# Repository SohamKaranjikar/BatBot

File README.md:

# BatBot
Hardware and Firmware for research regarding B2 (BatBot) under Post Doc. Jonathan Hoff and Prof.Joohyung Kim

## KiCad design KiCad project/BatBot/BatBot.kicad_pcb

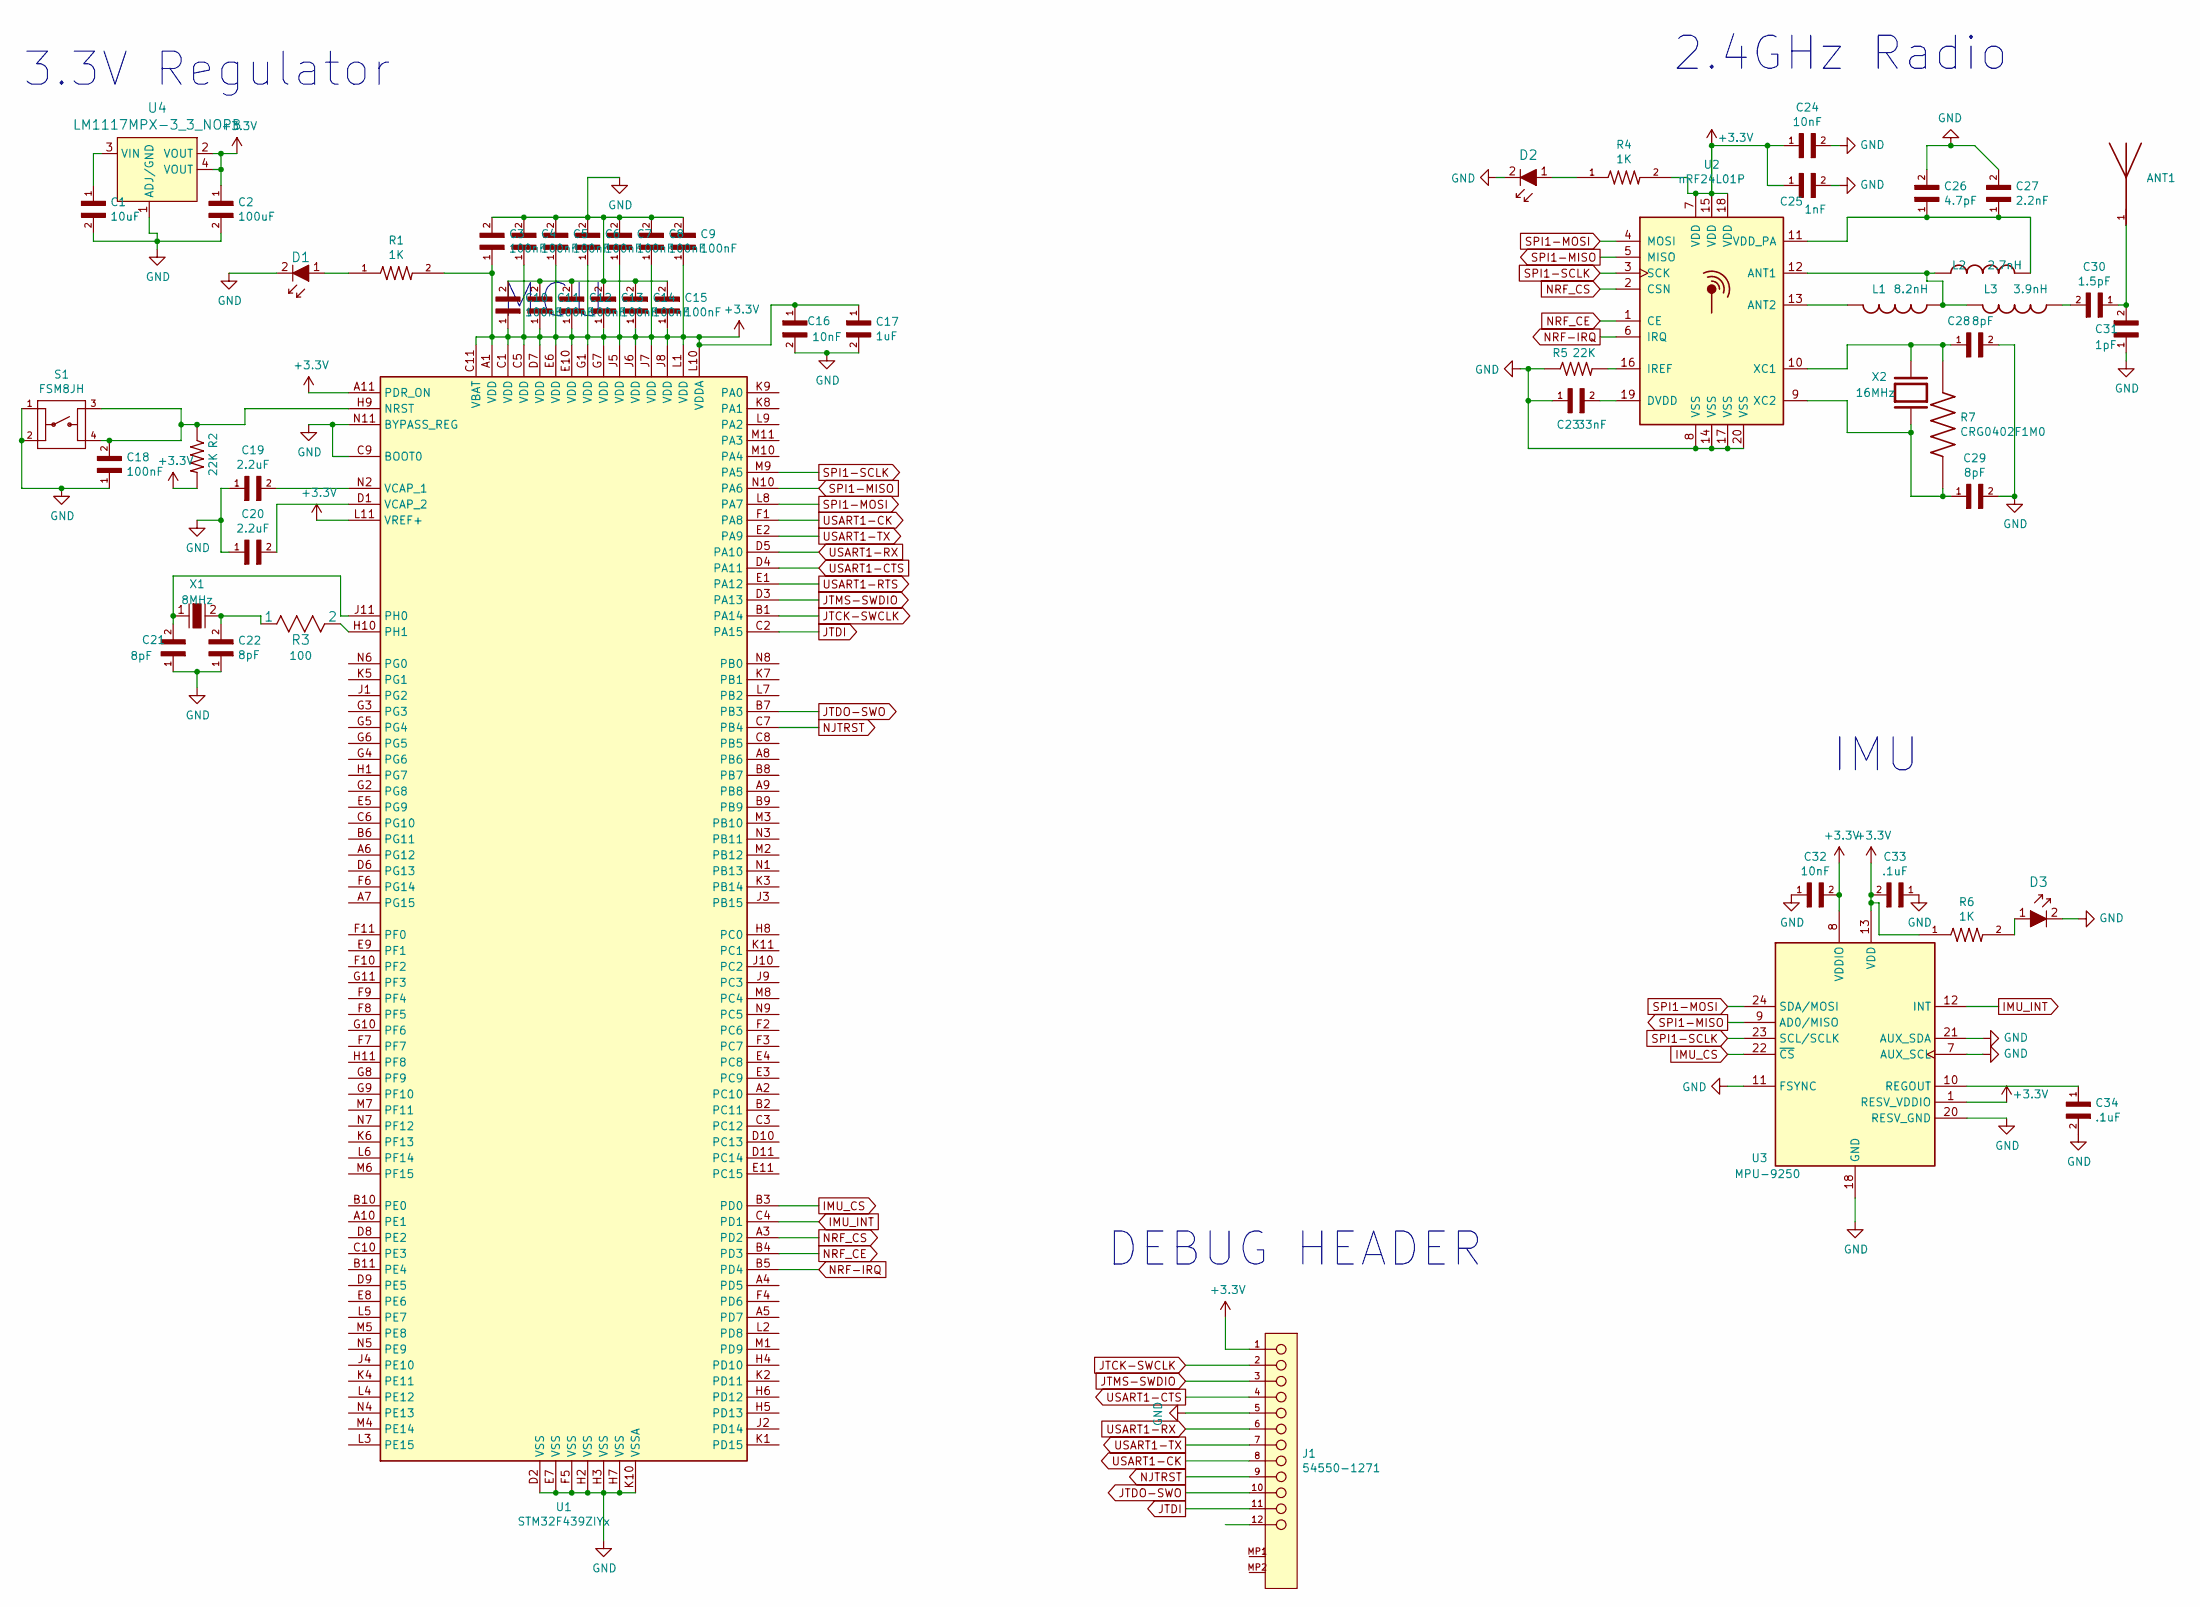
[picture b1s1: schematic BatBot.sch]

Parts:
ANT1: AMCA31-2R450G-S1F-T3; ANT_AMCA31-2R450G-S1F-T3
C1: GCJ21BR71A106KE01L; CAPC2012X145N
C2: CL31A107MQHNNNE; CAPC3216X180N
C3, C4, C5, C6, C7, C8, C9, C10, C11, C12, C13, C14, C15, C18: GCE21BR71H104KA01L; CAPC2012X145N
C16, C24, C32: 06035C103MAT2A; CAPC1608X90N
C17: GCM21BR11E105KA42L; CAPC2012X140N
C19, C20: GRM188C71E225KE11J; CAPC1608X100N
C21, C22, C28, C29: GRM0335C1H8R0DA01D; CAPC0603X33N
C23: 06035C333KAT2A; CAPC1608X90N
C25: 0402ZC102KAT2A; CAPC1005X56N
C26: CC0603BRNPO0BN4R7; CAPC1608X90
C27: EMK212B7225MG-T; CAPC2012X135N
C30: AC0402BRNPO9BN1R5; CAPC1005X55N
C31: CC0603CRNPO8BN1R0; CAPC1608X90
C33, C34: 0805YC104K4Z4A; CAPC2012X140N
D1, D2, D3: LTST-C190KRKT; 0603; MPN LTST-C190KRKT; Digi-Key_PN 160-1436-1-ND
J1: 54550-1271; Molex-54550-1271-Manufacturer_Recommended; Voltage Max 50V
L1: CE201210-8N2J; INDC2012X103N
L2: AQ1052N7S-T; INDC1006X55N
L3: AIMC-0805-3N9S-T; INDC2012X115N
R1, R4, R6: 1-1622826-8; RESC1005X35N
R2, R5: 8-1676481-3; RESC1608X50N
R3: RC0201FR-07100RL
R7: CRG0402F1M0; RESC1005X40N
S1: FSM8JH; SW_FSM8JH
U1: STM32F439ZIYx; ST_WLCSP-143_Die419
U2: nRF24L01P; QFN-20-1EP_4x4mm_P0.5mm_EP2.5x2.5mm
U3: MPU-9250; InvenSense_QFN-24_3x3mm_P0.4mm
U4: LM1117MPX-3_3_NOPB; SOT-223; MPN LM1117MPX-3.3/NOPB; Digi-Key_PN LM1117MPX-3.3/NOPBCT-ND
X1: NX3225GD-8MHZ-STD-CRA-3; SMD-2_3.2x2.5mm; MPN NX3225GD-8MHZ-STD-CRA-3; Digi-Key_PN 644-1178-1-ND
X2: XRCHA16M000F0A01R0; OSC_XRCHA16M000F0A01R0

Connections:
+3V3: C2.1, C3.1, C4.1, C5.1, C6.1, C7.1, C8.1, C9.1, C10.1, C11.1, C12.1, C13.1, C14.1, C15.1, C16.1, C17.1, C24.1, C25.1, C32.2, C33.2, J1.1, R1.2, R2.2, R4.2, R6.1, U1.A1 (VDD), U1.A11 (PDR_ON), U1.C1 (VDD), U1.C5 (VDD), U1.C11 (VBAT), U1.D7 (VDD), U1.E6 (VDD), U1.E10 (VDD), U1.G1 (VDD), U1.G7 (VDD), U1.J5 (VDD), U1.J6 (VDD), U1.J7 (VDD), U1.J8 (VDD), U1.L1 (VDD), U1.L10 (VDDA), U1.L11 (VREF+), U2.7 (VDD), U2.15 (VDD), U2.18 (VDD), U3.1 (RESV_VDDIO), U3.8 (VDDIO), U3.13 (VDD), U4.2 (VOUT), U4.4 (VOUT)
GND: C1.2, C2.2, C3.2, C4.2, C5.2, C6.2, C7.2, C8.2, C9.2, C10.2, C11.2, C12.2, C13.2, C14.2, C15.2, C16.2, C17.2, C18.1, C19.1, C20.1, C21.1, C22.1, C23.1, C24.2, C25.2, C26.2, C27.2, C28.2, C29.2, C31.1, C32.1, C33.1, C34.2, D1.2, D2.2, D3.2, J1.5, R5.1, S1.1, S1.2, U1.C9 (BOOT0), U1.D2 (VSS), U1.E7 (VSS), U1.F5 (VSS), U1.H2 (VSS), U1.H3 (VSS), U1.H7 (VSS), U1.K10 (VSSA), U1.N11 (BYPASS_REG), U2.8 (VSS), U2.14 (VSS), U2.17 (VSS), U2.20 (VSS), U3.7 (AUX_SCL), U3.11 (FSYNC), U3.18 (GND), U3.20 (RESV_GND), U3.21 (AUX_SDA), U4.1 (ADJ/GND)
IMU_CS: U1.B3 (PD0), U3.22 (~CS)
IMU_INT: U1.C4 (PD1), U3.12 (INT)
JTDO-SWO: J1.10, U1.B7 (PB3)
JTMS-SWDIO: J1.3, U1.D3 (PA13)
NJTRST: J1.9, U1.C7 (PB4)
NRF-IRQ: U1.B5 (PD4), U2.6 (IRQ)
NRF_CE: U1.B4 (PD3), U2.1 (CE)
NRF_CS: U1.A3 (PD2), U2.2 (CSN)
unnamed: ANT1.1, C30.1, C31.2
unnamed: C1.1, U4.3 (VIN)
unnamed: C18.2, R2.1, S1.3, S1.4, U1.H9 (NRST)
unnamed: C19.2, U1.N2 (VCAP_1)
unnamed: C20.2, U1.D1 (VCAP_2)
unnamed: C21.2, U1.J11 (PH0), X1.1
unnamed: C22.2, R3.1, X1.2
unnamed: C23.2, U2.19 (DVDD)
unnamed: C26.1, C27.1, L2.1, U2.11 (VDD_PA)
unnamed: C28.1, R7.1, U2.10 (XC1), X2.1
unnamed: C29.1, R7.2, U2.9 (XC2), X2.2
unnamed: C30.2, L3.2
unnamed: C34.1, U3.10 (REGOUT)
unnamed: D1.1, R1.1
unnamed: D2.1, R4.1
unnamed: D3.1, R6.2
unnamed: L1.1, U2.13 (ANT2)
unnamed: L1.2, L2.2, L3.1, U2.12 (ANT1)
unnamed: R3.2, U1.H10 (PH1)
unnamed: R5.2, U2.16 (IREF)
SPI1-MISO: U1.N10 (PA6), U2.5 (MISO), U3.9 (AD0/MISO)
SPI1-MOSI: U1.L8 (PA7), U2.4 (MOSI), U3.24 (SDA/MOSI)
SPI1-SCLK: U1.M9 (PA5), U2.3 (SCK), U3.23 (SCL/SCLK)
USART1-CK: J1.8, U1.F1 (PA8)
USART1-CTS: J1.4, U1.D4 (PA11)
USART1-RTS: U1.E1 (PA12)
USART1-RX: J1.6, U1.D5 (PA10)
USART1-TX: J1.7, U1.E2 (PA9)

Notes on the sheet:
2.4GHz Radio
IMU
3.3V Regulator
MCU
DEBUG HEADER

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
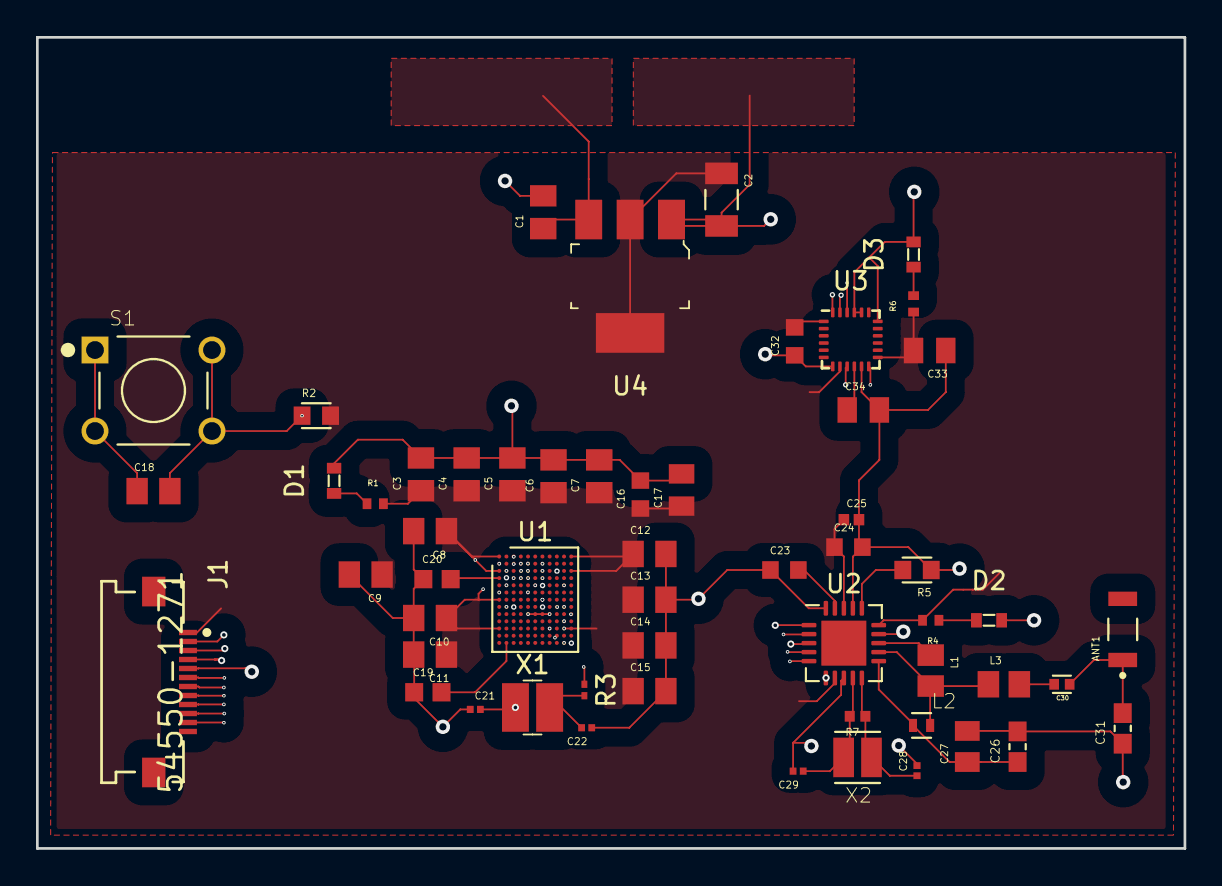
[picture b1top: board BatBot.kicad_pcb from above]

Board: 4 copper layers, 63.8 x 45.1 mm, 56 parts (0 on the bottom side), 38 nets.

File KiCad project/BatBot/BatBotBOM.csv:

"Source:","/Users/Soham/Desktop/School/ECE 397 B2/KiCad project/BatBot/BatBot.sch"
"Date:","Wednesday, September 30, 2020 at 10:15:36 PM"
"Tool:","Eeschema (5.1.6-0)"
"Component Count:","55"
"Ref","Value","Footprint","Datasheet","Manufacturer","Vendor"
"ANT1","AMCA31-2R450G-S1F-T3","ANT_AMCA31-2R450G-S1F-T3","1.4mm","",""
"C1","GCJ21BR71A106KE01L","CAPC2012X145N","","",""
"C2","CL31A107MQHNNNE","CAPC3216X180N","","",""
"C3","GCE21BR71H104KA01L","CAPC2012X145N","","",""
"C4","GCE21BR71H104KA01L","CAPC2012X145N","","",""
"C5","GCE21BR71H104KA01L","CAPC2012X145N","","",""
"C6","GCE21BR71H104KA01L","CAPC2012X145N","","",""
"C7","GCE21BR71H104KA01L","CAPC2012X145N","","",""
"C8","GCE21BR71H104KA01L","CAPC2012X145N","","",""
"C9","GCE21BR71H104KA01L","CAPC2012X145N","","",""
"C10","GCE21BR71H104KA01L","CAPC2012X145N","","",""
"C11","GCE21BR71H104KA01L","CAPC2012X145N","","",""
"C12","GCE21BR71H104KA01L","CAPC2012X145N","","",""
"C13","GCE21BR71H104KA01L","CAPC2012X145N","","",""
"C14","GCE21BR71H104KA01L","CAPC2012X145N","","",""
"C15","GCE21BR71H104KA01L","CAPC2012X145N","","",""
"C16","06035C103MAT2A","CAPC1608X90N","","",""
"C17","GCM21BR11E105KA42L","CAPC2012X140N","","",""
"C18","GCE21BR71H104KA01L","CAPC2012X145N","","",""
"C19","GRM188C71E225KE11J","CAPC1608X100N","","",""
"C20","GRM188C71E225KE11J","CAPC1608X100N","","",""
"C21","GRM0335C1H8R0DA01D","CAPC0603X33N","","",""
"C22","GRM0335C1H8R0DA01D","CAPC0603X33N","","",""
"C23","06035C333KAT2A","CAPC1608X90N","","",""
"C24","06035C103MAT2A","CAPC1608X90N","","",""
"C25","0402ZC102KAT2A","CAPC1005X56N","","",""
"C26","CC0603BRNPO0BN4R7","CAPC1608X90","","",""
"C27","EMK212B7225MG-T","CAPC2012X135N","","",""
"C28","GRM0335C1H8R0DA01D","CAPC0603X33N","","",""
"C29","GRM0335C1H8R0DA01D","CAPC0603X33N","","",""
"C30","AC0402BRNPO9BN1R5","CAPC1005X55N","","",""
"C31","CC0603CRNPO8BN1R0","CAPC1608X90","","",""
"C32","06035C103MAT2A","CAPC1608X90N","","",""
"C33","0805YC104K4Z4A","CAPC2012X140N","","",""
"C34","0805YC104K4Z4A","CAPC2012X140N","","",""
"D1","LTST-C190KRKT","digikey-footprints:0603","http://optoelectronics.liteon.com/upload/download/DS-22-99-0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","Lite-On Inc.",""
"D2","LTST-C190KRKT","digikey-footprints:0603","http://optoelectronics.liteon.com/upload/download/DS-22-99-0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","Lite-On Inc.",""
"D3","LTST-C190KRKT","digikey-footprints:0603","http://optoelectronics.liteon.com/upload/download/DS-22-99-0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","Lite-On Inc.",""
"J1","54550-1271","Molex-54550-1271-*","http://www.molex.com/webdocs/datasheets/pdf/en-us/0545501271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","",""
"L1","CE201210-8N2J","INDC2012X103N","","",""
"L2","AQ1052N7S-T","INDC1006X55N","","",""
"L3","AIMC-0805-3N9S-T","INDC2012X115N","","",""
"R1","1-1622826-8","RESC1005X35N","0402","",""
"R2","8-1676481-3","RESC1608X50N","Compliant","",""
"R3","RC0201FR-07100RL","YAG_R0201_YAG","","",""
"R4","1-1622826-8","RESC1005X35N","0402","",""
"R5","8-1676481-3","RESC1608X50N","Compliant","",""
"R6","1-1622826-8","RESC1005X35N","0402","",""
"S1","FSM8JH","SW_FSM8JH","C10","",""
"U1","STM32F439ZIYx","Package_CSP:ST_WLCSP-143_Die419","http://www.st.com/st-web-ui/static/active/en/resource/techni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","",""
"U2","nRF24L01P","Package_DFN_QFN:QFN-20-1EP_4x4mm_P0.5mm_EP2.5x2.5mm","http://www.nordicsemi.com/eng/content/download/2726/34069/fi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","",""
"U3","MPU-9250","Sensor_Motion:InvenSense_QFN-24_3x3mm_P0.4mm","https://store.invensense.com/datasheets/invensense/MPU9250RE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","",""
"U4","LM1117-3.3","","http://www.ti.com/lit/ds/symlink/lm1117.pdf","",""
"X1","NX3225GD-8MHZ-STD-CRA-3","digikey-footprints:SMD-2_3.2x2.5mm","http://www.ndk.com/images/products/catalog/c_NX3225GD-STD-CR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","NDK America, Inc.",""
"X2","XRCHA16M000F0A01R0","OSC_XRCHA16M000F0A01R0","Murata","",""

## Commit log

2020-10-02 finished draft board design, updated schematic
2020-10-02 fix all DRC errors, swap microvias to blind/burried/through
2020-10-08 fix via errors
2020-10-09 fix PCBways errors
2020-10-15 update vias/traces to match PCB way requirements
2020-10-15 update gerbers
2020-10-15 4/4mil spacing update

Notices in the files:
parts and their libraries:
Copyright 2016 Accelerated Designs. All rights reserved.
